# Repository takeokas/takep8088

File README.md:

# takep8088
8088 Single Board Computer  

## Spec  
- S-RAM 1MBytes  
--  全メモリ空間  
-- AS6C4008-55PCN (512KW×8bit)2チップ  
-- リセット直後は、メモリ空間の後半 512K は、ROM  
-- 出力ポートのアクセスで、後半512KをROM/RAM切り替え  

- ROM 64Bytes  
-- SST 27SF512(EEPROM)  
-- 27C512互換であれば使用可能、2764あたりからそのまま差し込めるはず  

- SIO 8251(USART)  
-- ジャンパ J1 で、ボーレート用クロックの周波数を選択可能  
-- 秋月で販売されている FTDI USBシリアル変換ケーブル(5V) が直接 差せる  
--  https://akizukidenshi.com/catalog/g/g105841/    

- フリーランニング・タイマ  
  18.75Hz / 9.375Hz を JP1 で、選択可能  

- Crystal 14.7456MHz  
-- 8251(USART) の baud rate generation に、いい感じの周波数  
-- CPU は、約 4.9MHz で動作  
-- 周辺IOのクロックは、約2.45MHz  

## ボード  

- ジャンパ J1  
-- 8251(USART)のボーレート・ジェネレータの周波数選択  
  19200/9600/4800 bps  (f/1の場合)  
  
- ジャンパ JP1  
-- フリーランニング・タイマの周期選択  
  18.75Hz / 9.375Hz

- ワイヤリング  

-- 8251 TX Empty割込みを使用する場合は、7405 の空き入力端子に、8251-TXE を接続する  
-- 7405 の空き入力ピンは、(手配線などで) 必ず GND へ、接続する。さもないと、Interrupt Enableした途端に、割込みが発生する。  
-- U20 74139が、74HC139 のときは、空き入力ピンを、DT-R、SS0 に接続すること。74LS139など TTL のときは、open のママでも支障ない。  

※ワイヤがあるのは、設計どおり  
-- PCBレイアウト中に、引き回しを諦めただけ…orz  

## 回路
### 7405: 割込み 要求  
-- 7405の入力は、反転されて、すべてワイアードORして反転して、8088のINT(割込み要求)に接続  
-- 7405のopenな端子は、自分で(手ハンダで?)、PullDownの必要あり  
-- 後から付けた機器からの割込み要求は、7405の空き端子に接続するとよい  

### 8251 TX Empty 割込み 要求  
-- 8251の RX割込みは、PCBで7405に接続済み  
-- 8251の TXE(empty)割込み使うよね!  
-- 自分で、7405 に配線してください ＼(^^;／  
-- PCBのレイアウトを諦めた=それが設計だっ  

### 余りゲート  
-- U1,74LS14: B(3,4),C(5,6),F(13,12)  
-- U12,74LS00: A(1,2,3),B(4,5,6)  
-- U24,74LS00: C(10,9,8),D(13,12,11)  
-- U23,74LS74: B(8-13)  

## IOポート  
###  IO port address  

   00-03 : usart0 (rw) USART レジスタ; 通常 00と01 を使用する  
   04-07 : sw1 (rd);  D0: SWの値を読む, D1: timerIRQ の確認  
   08-0B : timer-irq-clr (wr); timer IRQのクリア  
   0C-0F : sysreg (wr),D0:/rom0-ena=0でROM, 1でRAM1, D1:timer-int-ena=1でtimer割込み可, D2:led2, D3:led3  
  
   10-13 : inport2(rd),  D0: U18[2pin]=NC, D1:U18[4pin]=NC;U18=74LS367  
   14-17 :   
   18-1B :   
   1C-1F :   
   
### IO port 説明  
- sysreg (WR) 0x0C ; U5,74LS174  
-- D0: /rom0-ena (reset:0), 0:ROM0 / 1:RAM1 (メモリ空間後半 A19==1 を ROM/RAM切り替え)  
-- D1: timer-int-ena (reset:0), 0:disable / 1:enable  
-- D2: LED2 (resetで0, 点灯)  
-- D3: LED3 (resetで0, 点灯)  
-- D4: (U5 Q4)Open  
-- D5: (U5 Q5)Open  
  
- SW1 (RD) 0x04  
-- D0: SW  
-- D1 : free running timer IRQ 読み出し  
  
- timer-irq-clr  (WR) 0x08  
-- free running timer INT clear  
-- 1/(2^18) カウンタ割り込みクリア  
  
- inport2(rd) 0x10  
-- U18=74LS367  
-- D0: U18[2pin]=NC, D1:U18[4pin]=NC;  
-- D2: U18[6pin]=NC, D5:U18[10pin]=NC;   
※D3,D4 は飛ばしている(配線の困難性から)

## その他  
- HOLD を、Vcc に、手動で接続してみると、CPU の実行が停止し、HLDA LEDが点灯する  
- HOLD を使用する機器は、HOLD 端子に接続するとよい(PCB では、Pull Downしているのみ)
- 2026/MAR/20 「Kernel/VM探検隊＠つくば No3」での、発表資料  
--  https://www.slideshare.net/slideshow/tht-8088-single-board-computer-with-amd-8088-bought-at-junk-shop-in-1989/286593537?utm_source=clipboard_share_button&utm_campaign=slideshare_make_sharing_viral_v2&utm_variation=control&utm_medium=share
-

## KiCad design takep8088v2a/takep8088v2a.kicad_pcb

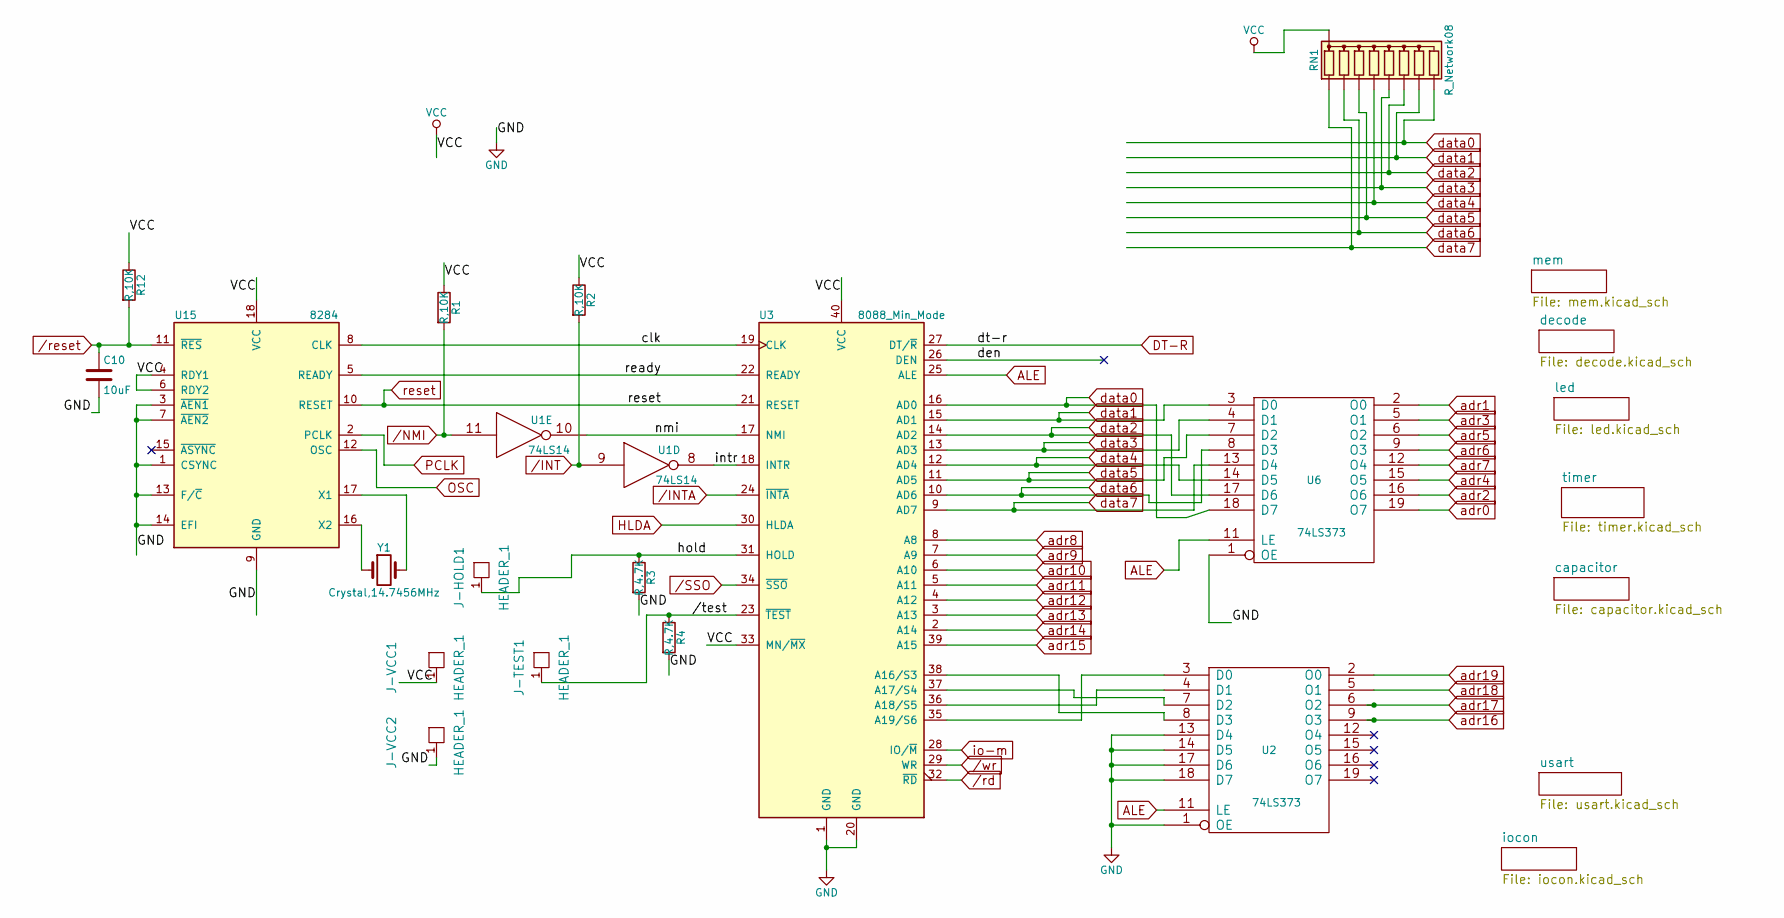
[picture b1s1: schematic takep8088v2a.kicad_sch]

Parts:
C10: 10uF; C_Disc_D3.0mm_W2.0mm_P2.50mm
J-HOLD1: HEADER_1; PinHeader_1x01_P2.54mm_Vertical
J-TEST1: HEADER_1; PinHeader_1x01_P2.54mm_Vertical
J-VCC1, J-VCC2: HEADER_1; PinHeader_1x01_P2.54mm_Vertical
R1, R2, R12: R,10K; R_Axial_DIN0207_L6.3mm_D2.5mm_P2.54mm_Vertical
R3, R4: R,4.7K; R_Axial_DIN0204_L3.6mm_D1.6mm_P5.08mm_Horizontal
RN1: R_Network08; R_Array_SIP9
U1: 74LS14; DIP-14_W7.62mm
U2, U6: 74LS373; DIP-20_W7.62mm
U3: 8088_Min_Mode; DIP-40_W15.24mm_Socket
U15: 8284; DIP-18_W7.62mm
Y1: Crystal,14.7456MHz; Crystal_HC49-4H_Vertical

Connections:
/clk: U3.19 (CLK), U15.8 (CLK)
/den: U3.26 (DEN)
/hold: J-HOLD1.1, R3.1, U3.31 (HOLD)
/intr: U1.8, U3.18 (INTR)
/nmi: U1.10, U3.17 (NMI)
/ready: U3.22 (READY), U15.5 (READY)
//test: J-TEST1.1, R4.1, U3.23 (~TEST)
ALE: U2.11 (LE), U3.25 (ALE), U6.11 (LE)
DT-R: U3.27 (DT/~R); also elsewhere on the board
GND: C10.2, J-VCC2.1, R3.2, R4.2, U1.7 (GND), U2.1 (OE), U2.10 (GND), U2.13 (D4), U2.14 (D5), U2.17 (D6), U2.18 (D7), U3.1 (GND), U3.20 (GND), U6.1 (OE), U6.10 (GND), U15.1 (CSYNC), U15.3 (~AEN1), U15.7 (~AEN2), U15.9 (GND), U15.13 (F/~C), U15.14 (EFI); also elsewhere on the board
HLDA: U3.30 (HLDA); also elsewhere on the board
unnamed: U2.3 (D0), U3.35 (A19/S6)
unnamed: U2.4 (D1), U3.36 (A18/S5)
unnamed: U2.7 (D2), U3.37 (A17/S4)
unnamed: U2.8 (D3), U3.38 (A16/S3)
unnamed: U15.17 (X1), Y1.2
unnamed: U15.16 (X2), Y1.1
OSC: U15.12 (OSC)
PCLK: U15.2 (PCLK); also elsewhere on the board
VCC: J-VCC1.1, R1.1, R2.1, R12.1, RN1.1 (common), U1.14 (VCC), U2.20 (VCC), U3.33 (MN/~MX), U3.40 (VCC), U6.20 (VCC), U15.4 (RDY1), U15.6 (RDY2), U15.18 (VCC); also elsewhere on the board
adr0: U6.19 (O7); also elsewhere on the board
adr1: U6.2 (O0); also elsewhere on the board
adr2: U6.16 (O6); also elsewhere on the board
adr3: U6.5 (O1); also elsewhere on the board
adr4: U6.15 (O5); also elsewhere on the board
adr5: U6.6 (O2); also elsewhere on the board
adr6: U6.9 (O3); also elsewhere on the board
adr7: U6.12 (O4); also elsewhere on the board
adr8: U3.8 (A8); also elsewhere on the board
adr9: U3.7 (A9); also elsewhere on the board
adr10: U3.6 (A10); also elsewhere on the board
adr11: U3.5 (A11); also elsewhere on the board
adr12: U3.4 (A12); also elsewhere on the board
adr13: U3.3 (A13); also elsewhere on the board
adr14: U3.2 (A14); also elsewhere on the board
adr15: U3.39 (A15); also elsewhere on the board
adr16: U2.9 (O3); also elsewhere on the board
adr17: U2.6 (O2); also elsewhere on the board
adr18: U2.5 (O1); also elsewhere on the board
adr19: U2.2 (O0); also elsewhere on the board
data0: RN1.9 (R8), U3.16 (AD0), U6.18 (D7); also elsewhere on the board
data1: RN1.8 (R7), U3.15 (AD1), U6.3 (D0); also elsewhere on the board
data2: RN1.7 (R6), U3.14 (AD2), U6.17 (D6); also elsewhere on the board
data3: RN1.6 (R5), U3.13 (AD3), U6.4 (D1); also elsewhere on the board
data4: RN1.5 (R4), U3.12 (AD4), U6.14 (D5); also elsewhere on the board
data5: RN1.4 (R3), U3.11 (AD5), U6.7 (D2); also elsewhere on the board
data6: RN1.3 (R2), U3.10 (AD6), U6.8 (D3); also elsewhere on the board
data7: RN1.2 (R1), U3.9 (AD7), U6.13 (D4); also elsewhere on the board
io-m: U3.28 (IO/~M); also elsewhere on the board
reset: U3.21 (RESET), U15.10 (RESET); also elsewhere on the board
/INT: R2.2, U1.9; also elsewhere on the board
/INTA: U3.24 (~INTA); also elsewhere on the board
/NMI: R1.2, U1.11; also elsewhere on the board
/SSO: U3.34 (~SSO); also elsewhere on the board
/rd: U3.32 (~RD); also elsewhere on the board
/reset: C10.1, R12.2, U15.11 (~RES); also elsewhere on the board
/wr: U3.29 (WR); also elsewhere on the board

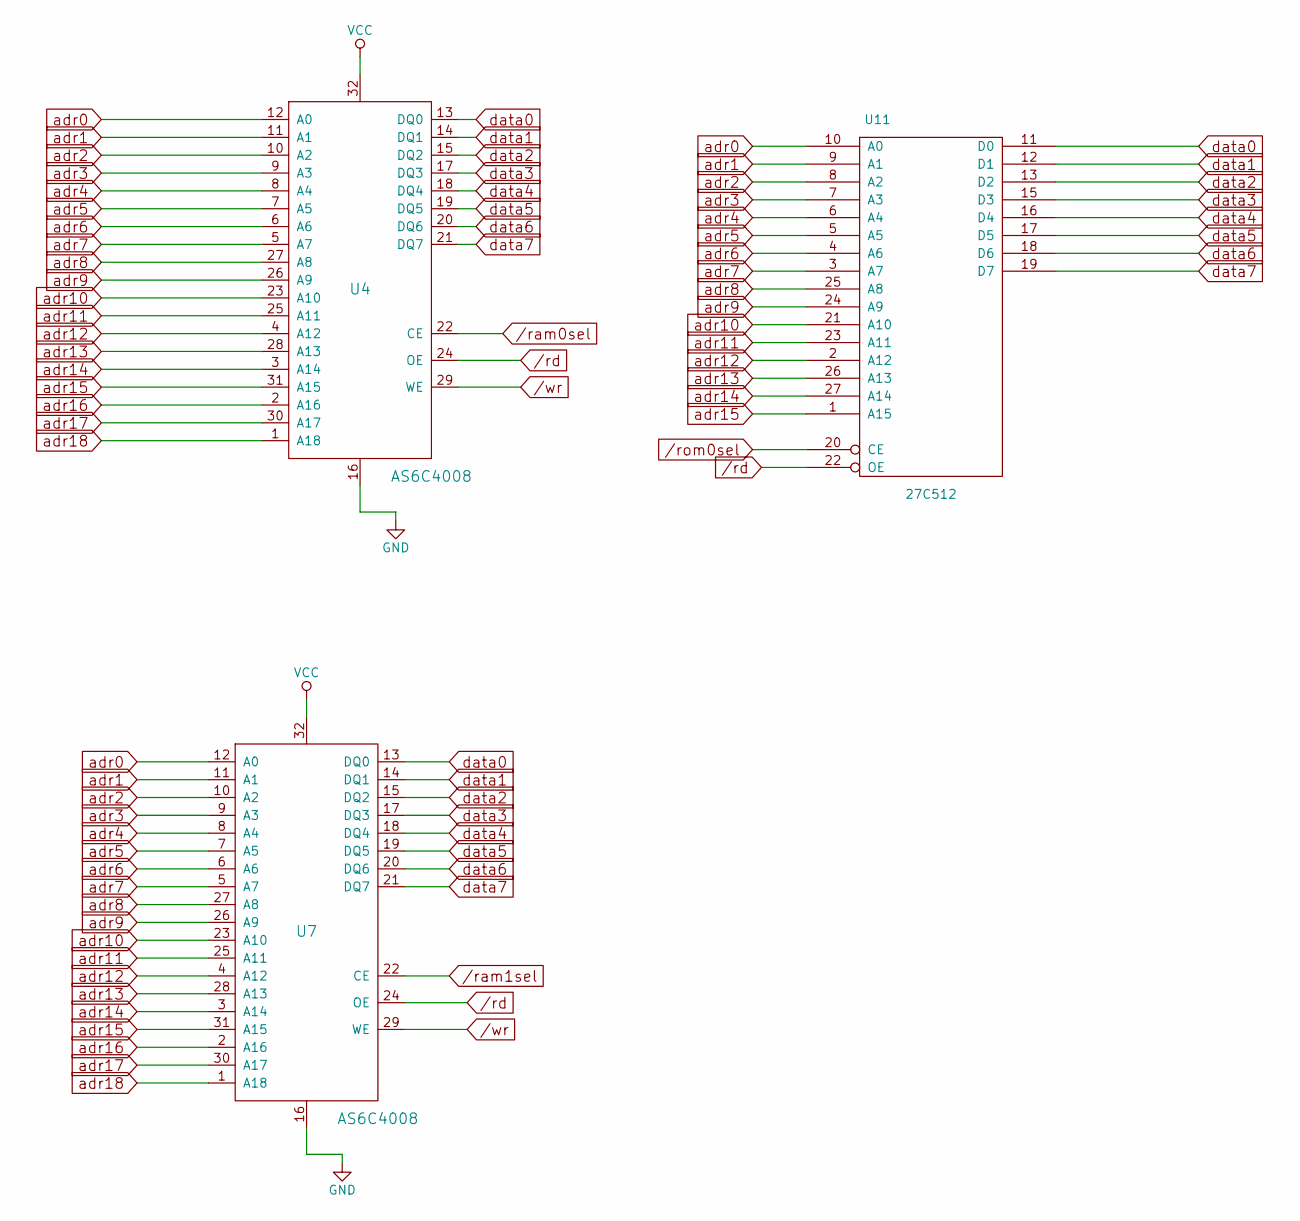
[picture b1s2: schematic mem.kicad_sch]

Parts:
U4, U7: AS6C4008; DIP-32_W15.24mm
U11: 27C512; DIP-28_W15.24mm

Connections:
GND: U4.16, U7.16, U11.14 (GND); also elsewhere on the board
VCC: U4.32, U7.32, U11.28 (VCC); also elsewhere on the board
adr0: U4.12 (A0), U7.12 (A0), U11.10 (A0); also elsewhere on the board
adr1: U4.11 (A1), U7.11 (A1), U11.9 (A1); also elsewhere on the board
adr2: U4.10 (A2), U7.10 (A2), U11.8 (A2); also elsewhere on the board
adr3: U4.9 (A3), U7.9 (A3), U11.7 (A3); also elsewhere on the board
adr4: U4.8 (A4), U7.8 (A4), U11.6 (A4); also elsewhere on the board
adr5: U4.7 (A5), U7.7 (A5), U11.5 (A5); also elsewhere on the board
adr6: U4.6 (A6), U7.6 (A6), U11.4 (A6); also elsewhere on the board
adr7: U4.5 (A7), U7.5 (A7), U11.3 (A7); also elsewhere on the board
adr8: U4.27 (A8), U7.27 (A8), U11.25 (A8); also elsewhere on the board
adr9: U4.26 (A9), U7.26 (A9), U11.24 (A9); also elsewhere on the board
adr10: U4.23 (A10), U7.23 (A10), U11.21 (A10); also elsewhere on the board
adr11: U4.25 (A11), U7.25 (A11), U11.23 (A11); also elsewhere on the board
adr12: U4.4 (A12), U7.4 (A12), U11.2 (A12); also elsewhere on the board
adr13: U4.28 (A13), U7.28 (A13), U11.26 (A13); also elsewhere on the board
adr14: U4.3 (A14), U7.3 (A14), U11.27 (A14); also elsewhere on the board
adr15: U4.31 (A15), U7.31 (A15), U11.1 (A15); also elsewhere on the board
adr16: U4.2 (A16), U7.2 (A16); also elsewhere on the board
adr17: U4.30 (A17), U7.30 (A17); also elsewhere on the board
adr18: U4.1 (A18), U7.1 (A18); also elsewhere on the board
data0: U4.13 (DQ0), U7.13 (DQ0), U11.11 (D0); also elsewhere on the board
data1: U4.14 (DQ1), U7.14 (DQ1), U11.12 (D1); also elsewhere on the board
data2: U4.15 (DQ2), U7.15 (DQ2), U11.13 (D2); also elsewhere on the board
data3: U4.17 (DQ3), U7.17 (DQ3), U11.15 (D3); also elsewhere on the board
data4: U4.18 (DQ4), U7.18 (DQ4), U11.16 (D4); also elsewhere on the board
data5: U4.19 (DQ5), U7.19 (DQ5), U11.17 (D5); also elsewhere on the board
data6: U4.20 (DQ6), U7.20 (DQ6), U11.18 (D6); also elsewhere on the board
data7: U4.21 (DQ7), U7.21 (DQ7), U11.19 (D7); also elsewhere on the board
/ram0sel: U4.22 (CE); also elsewhere on the board
/ram1sel: U7.22 (CE); also elsewhere on the board
/rd: U4.24 (OE), U7.24 (OE), U11.22 (OE); also elsewhere on the board
/rom0sel: U11.20 (CE); also elsewhere on the board
/wr: U4.29 (WE), U7.29 (WE); also elsewhere on the board

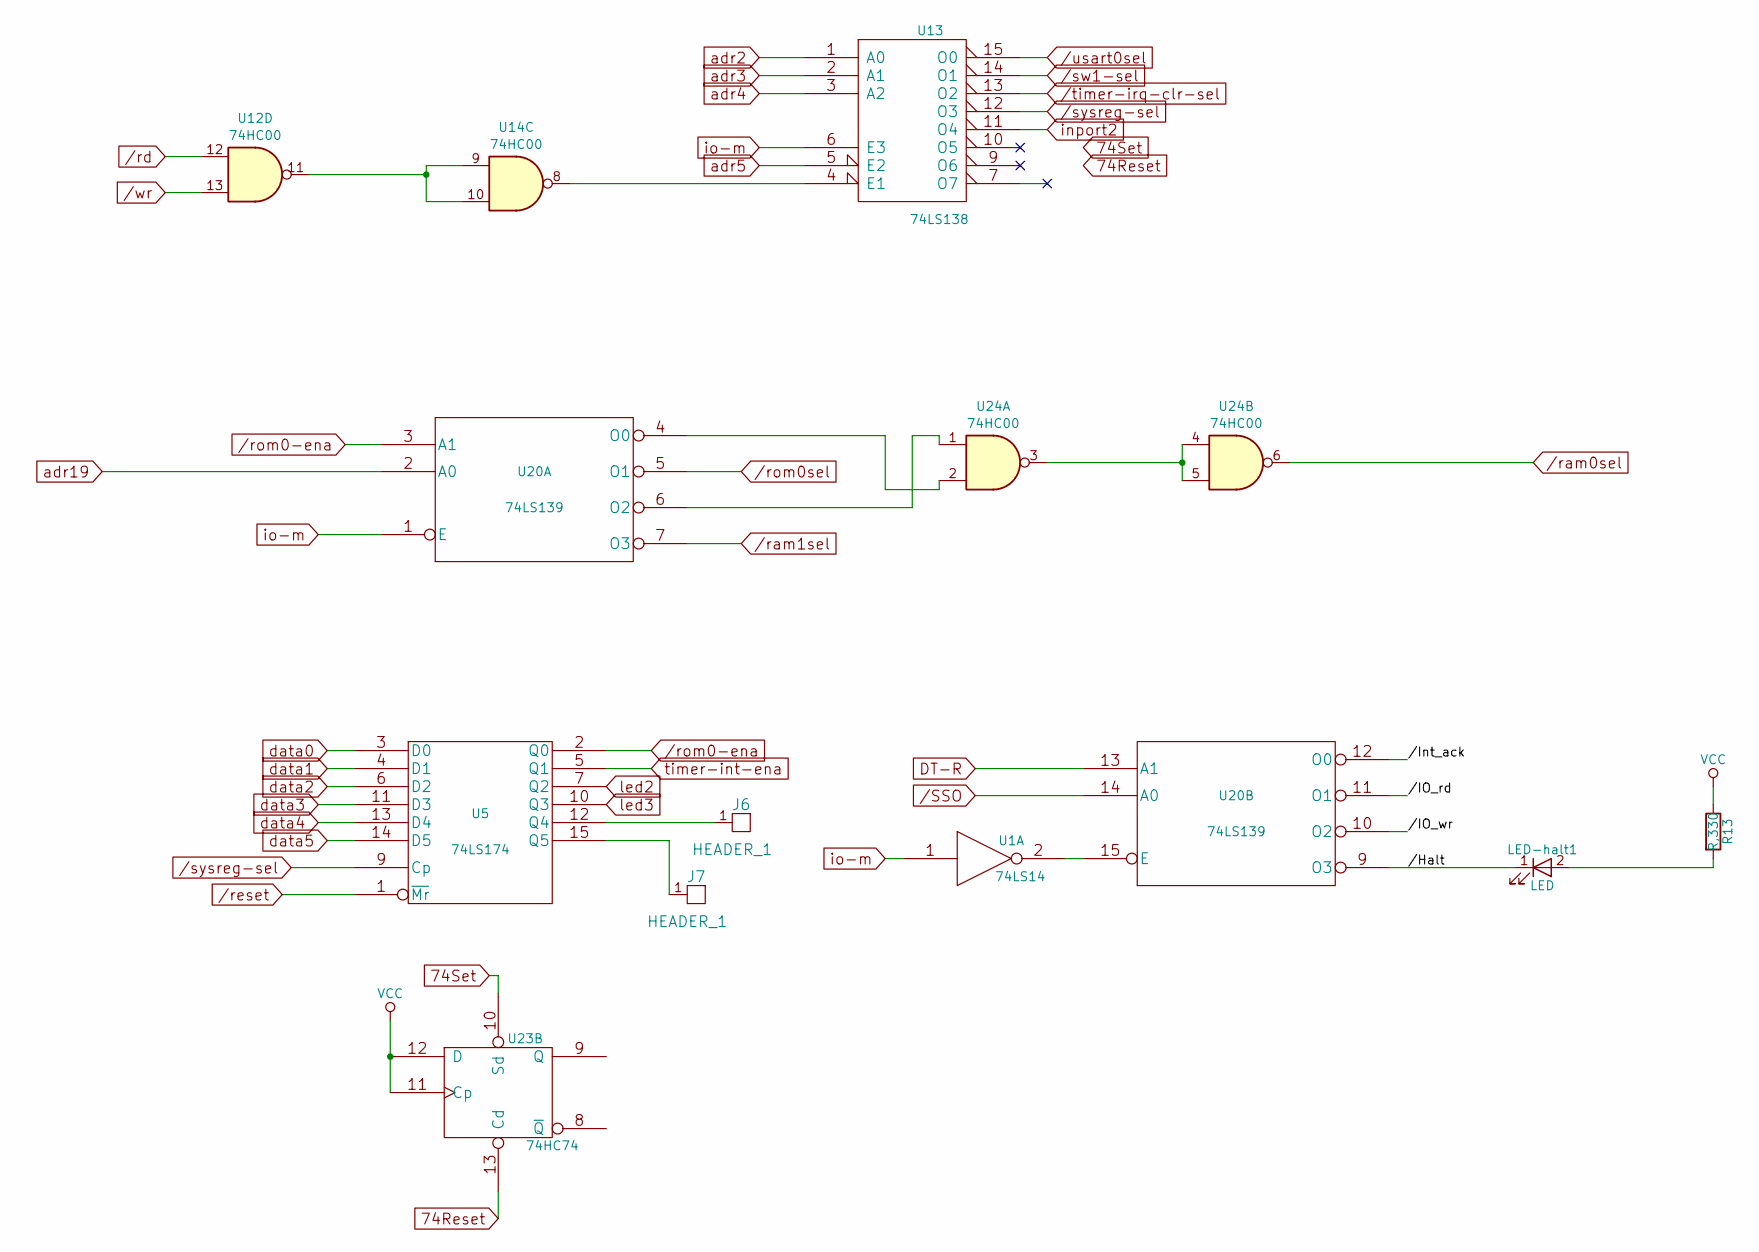
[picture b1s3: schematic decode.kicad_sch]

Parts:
J6, J7: HEADER_1; PinHeader_1x01_P2.54mm_Vertical
LED-halt1: LED; LED_D1.8mm_W3.3mm_H2.4mm
R13: R,330; R_Axial_DIN0207_L6.3mm_D2.5mm_P2.54mm_Vertical
U1: 74LS14; DIP-14_W7.62mm
U5: 74LS174; DIP-16_W7.62mm
U12, U14, U24: 74HC00
U13: 74LS138; DIP-16_W7.62mm
U20: 74LS139; DIP-16_W7.62mm
U23: 74HC74; DIP-14_W7.62mm

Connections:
74Reset: U23.13 (Cd)
74Set: U23.10 (Sd)
/decode//Halt: LED-halt1.1 (K), U20.9 (O3)
/decode//IO_rd: U20.11 (O1)
/decode//IO_wr: U20.10 (O2)
/decode//Int_ack: U20.12 (O0)
DT-R: U20.13 (A1); also elsewhere on the board
GND: U1.7 (GND), U5.8 (GND), U12.7 (GND), U13.8 (GND), U20.8 (GND), U23.7 (GND), U24.7 (GND); also elsewhere on the board
unnamed: LED-halt1.2 (A), R13.2
unnamed: J6.1, U5.12 (Q4)
unnamed: J7.1, U5.15 (Q5)
unnamed: U12.9, U12.10, U12.11, U14.9, U14.10
unnamed: U12.8, U13.4 (E1), U14.8
unnamed: U20.4 (O0), U24.2
unnamed: U20.6 (O2), U24.1
unnamed: U1.2, U20.15 (E)
unnamed: U24.3, U24.4, U24.5
VCC: R13.1, U1.14 (VCC), U5.16 (VCC), U12.14 (VCC), U13.16 (VCC), U20.16 (VCC), U23.11 (Cp), U23.12 (D), U23.14 (VCC), U24.14 (VCC); also elsewhere on the board
adr2: U13.1 (A0); also elsewhere on the board
adr3: U13.2 (A1); also elsewhere on the board
adr4: U13.3 (A2); also elsewhere on the board
adr5: U13.5 (E2); also elsewhere on the board
adr19: U20.2 (A0); also elsewhere on the board
data0: U5.3 (D0); also elsewhere on the board
data1: U5.4 (D1); also elsewhere on the board
data2: U5.6 (D2); also elsewhere on the board
data3: U5.11 (D3); also elsewhere on the board
data4: U5.13 (D4); also elsewhere on the board
data5: U5.14 (D5); also elsewhere on the board
inport2: U13.11 (O4); also elsewhere on the board
io-m: U1.1, U13.6 (E3), U20.1 (E); also elsewhere on the board
led2: U5.7 (Q2); also elsewhere on the board
led3: U5.10 (Q3); also elsewhere on the board
timer-int-ena: U5.5 (Q1); also elsewhere on the board
/SSO: U20.14 (A0); also elsewhere on the board
/ram0sel: U24.6; also elsewhere on the board
/ram1sel: U20.7 (O3); also elsewhere on the board
/rd: U12.12; also elsewhere on the board
/reset: U5.1 (~Mr); also elsewhere on the board
/rom0-ena: U5.2 (Q0), U20.3 (A1); also elsewhere on the board
/rom0sel: U20.5 (O1); also elsewhere on the board
/sw1-sel: U13.14 (O1); also elsewhere on the board
/sysreg-sel: U5.9 (Cp), U13.12 (O3)
/timer-irq-clr-sel: U13.13 (O2); also elsewhere on the board
/usart0sel: U13.15 (O0); also elsewhere on the board
/wr: U12.13; also elsewhere on the board

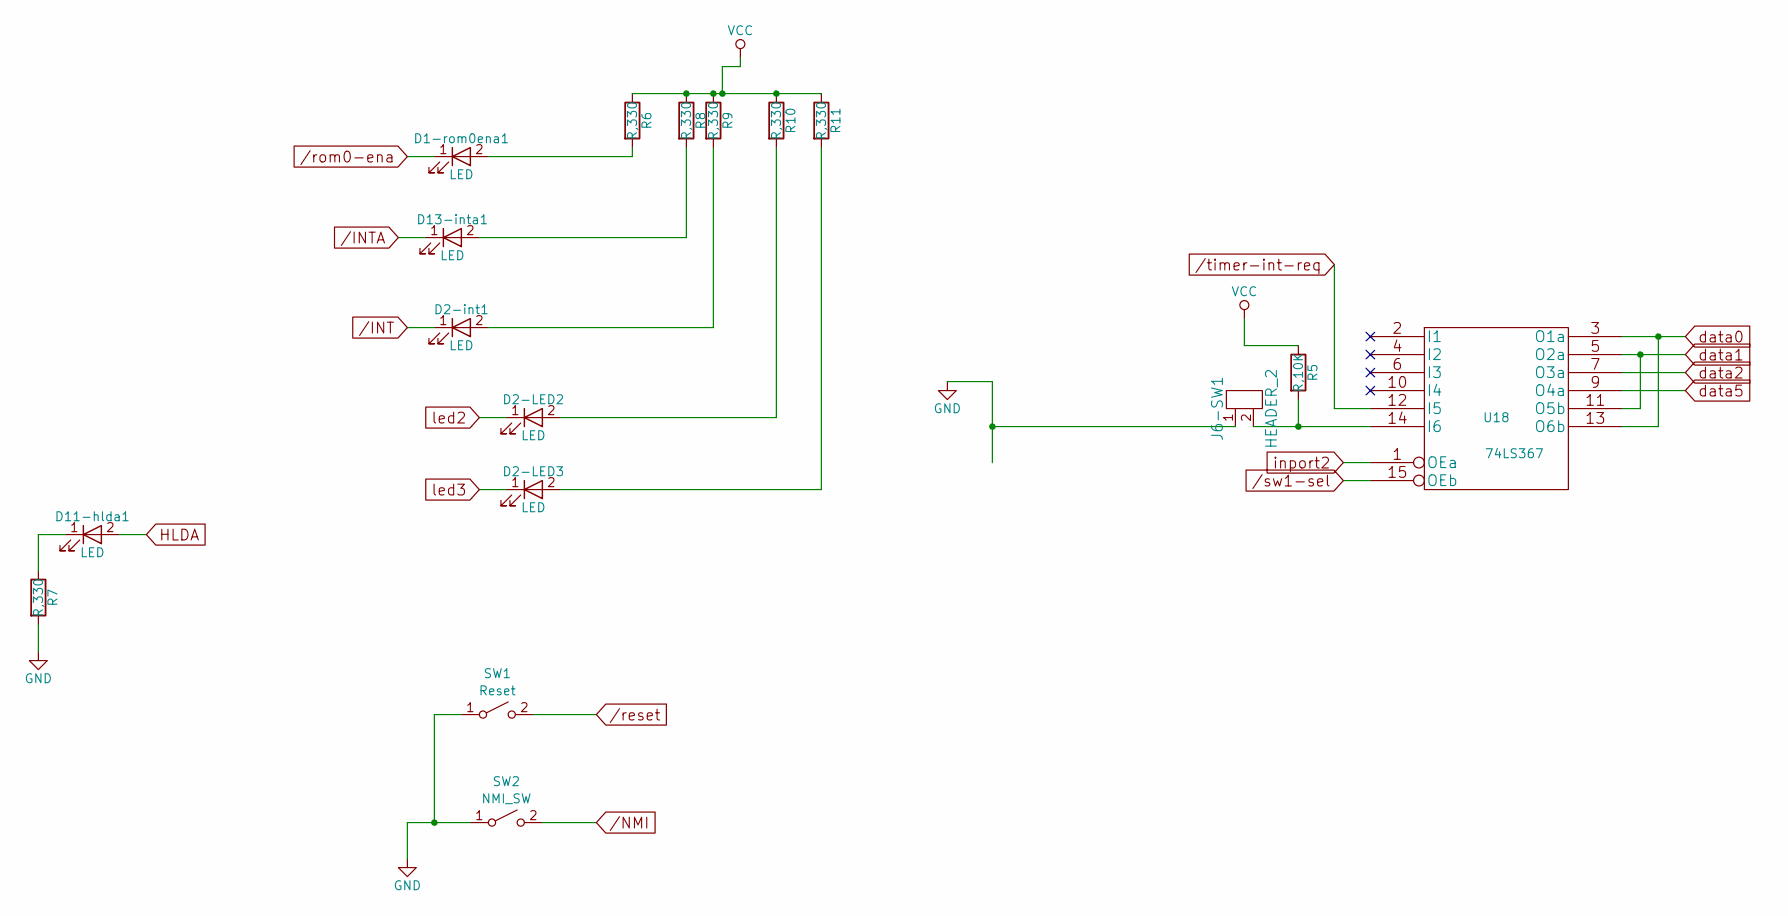
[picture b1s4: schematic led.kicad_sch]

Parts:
D1-rom0ena1, D2-LED2, D2-LED3, D2-int1, D11-hlda1, D13-inta1: LED; LED_D1.8mm_W3.3mm_H2.4mm
J6-SW1: HEADER_2; PinHeader_2x01_P2.54mm_Vertical
R5: R,10K; R_Axial_DIN0207_L6.3mm_D2.5mm_P2.54mm_Vertical
R6, R7, R8, R9, R10, R11: R,330; R_Axial_DIN0207_L6.3mm_D2.5mm_P2.54mm_Vertical
SW1: Reset; SW_PUSH_1P1T_6x3.5mm_H5.0_APEM_MJTP1250
SW2: NMI_SW; SW_PUSH_1P1T_6x3.5mm_H5.0_APEM_MJTP1250
U18: 74LS367; DIP-16_W7.62mm

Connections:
GND: J6-SW1.1, R7.2, SW1.1 (A), SW2.1 (A), U18.8 (GND); also elsewhere on the board
HLDA: D11-hlda1.2 (A); also elsewhere on the board
unnamed: D1-rom0ena1.2 (A), R6.2
unnamed: D2-LED2.2 (A), R10.2
unnamed: D2-LED3.2 (A), R11.2
unnamed: D2-int1.2 (A), R9.2
unnamed: D11-hlda1.1 (K), R7.1
unnamed: D13-inta1.2 (A), R8.2
unnamed: J6-SW1.2, R5.2, U18.14 (I6)
VCC: R5.1, R6.1, R8.1, R9.1, R10.1, R11.1, U18.16 (VCC); also elsewhere on the board
data0: U18.3 (O1a), U18.13 (O6b); also elsewhere on the board
data1: U18.5 (O2a), U18.11 (O5b); also elsewhere on the board
data2: U18.7 (O3a); also elsewhere on the board
data5: U18.9 (O4a); also elsewhere on the board
inport2: U18.1 (OEa); also elsewhere on the board
led2: D2-LED2.1 (K); also elsewhere on the board
led3: D2-LED3.1 (K); also elsewhere on the board
/INT: D2-int1.1 (K); also elsewhere on the board
/INTA: D13-inta1.1 (K); also elsewhere on the board
/NMI: SW2.2 (B); also elsewhere on the board
/reset: SW1.2 (B); also elsewhere on the board
/rom0-ena: D1-rom0ena1.1 (K); also elsewhere on the board
/sw1-sel: U18.15 (OEb); also elsewhere on the board
/timer-int-req: U18.12 (I5); also elsewhere on the board

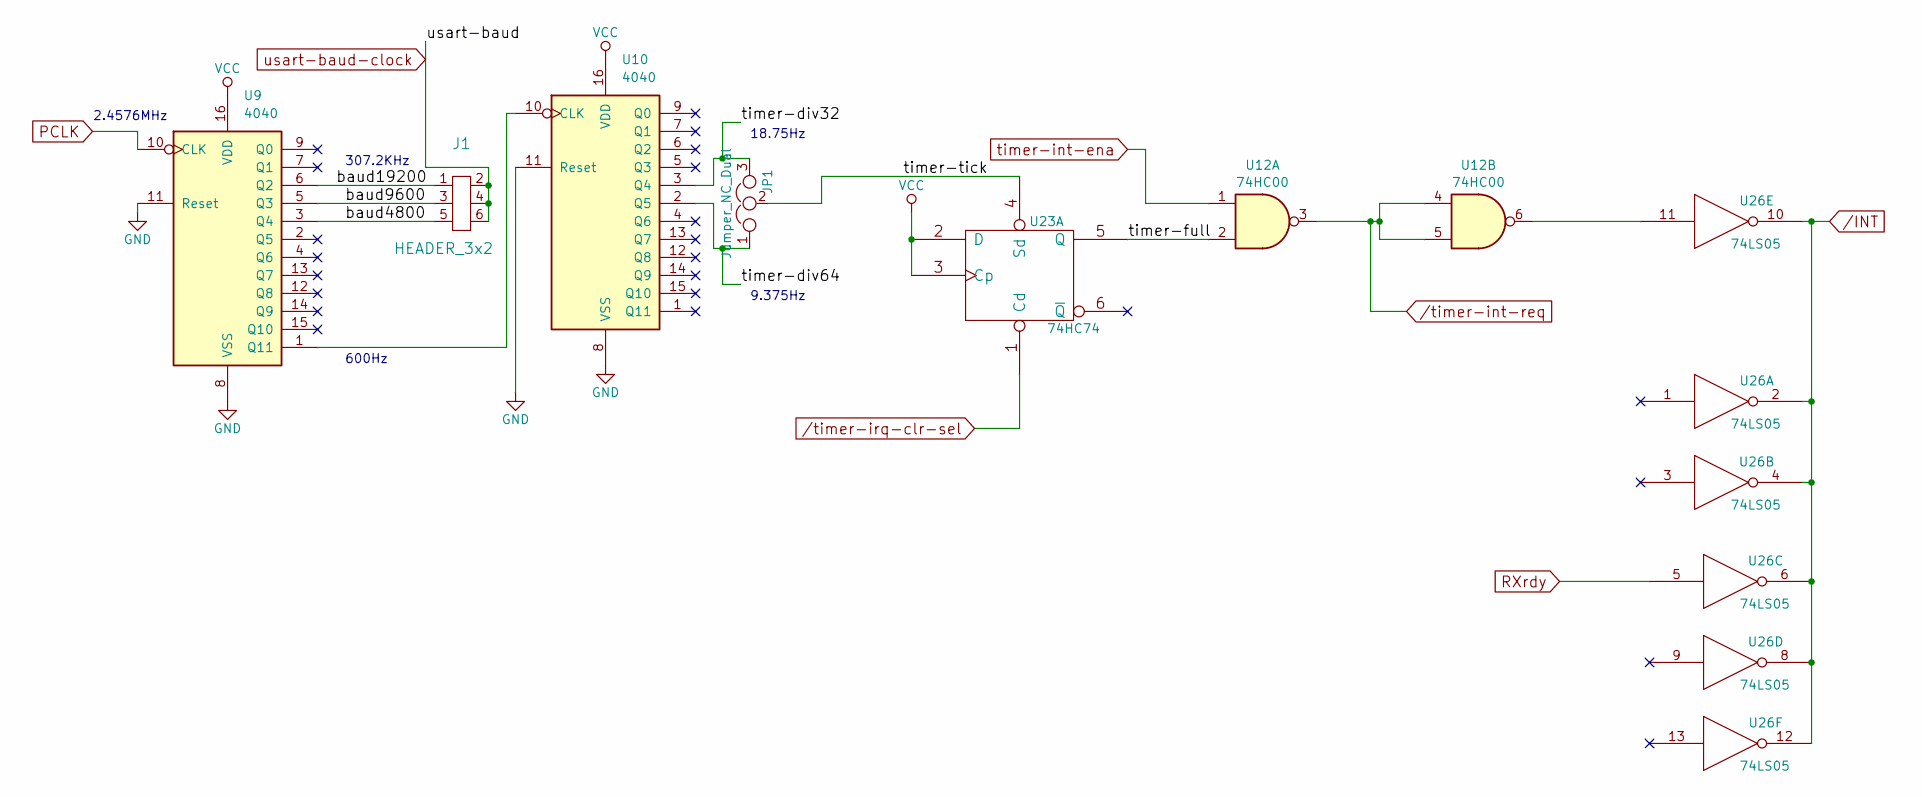
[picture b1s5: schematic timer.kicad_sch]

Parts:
J1: HEADER_3x2; PinHeader_2x03_P2.54mm_Vertical
JP1: Jumper_NC_Dual; PinHeader_1x03_P2.54mm_Vertical
U9, U10: 4040; DIP-16_W7.62mm
U12: 74HC00
U23: 74HC74; DIP-14_W7.62mm
U26: 74LS05; DIP-14_W7.62mm

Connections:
/timer/baud4800: J1.5, U9.3 (Q4)
/timer/baud9600: J1.3, U9.5 (Q3)
/timer/baud19200: J1.1, U9.6 (Q2)
/timer/timer-div32: JP1.3, U10.3 (Q4)
/timer/timer-div64: JP1.1, U10.2 (Q5)
/timer/timer-full: U12.2, U23.5 (Q)
/timer/timer-tick: JP1.2, U23.4 (Sd)
GND: U9.8 (VSS), U9.11 (Reset), U10.8 (VSS), U10.11 (Reset), U12.7 (GND), U23.7 (GND), U26.7 (GND); also elsewhere on the board
unnamed: U9.1 (Q11), U10.10 (CLK)
unnamed: U12.6, U26.11
unnamed 48: U12.9, U12.10; also elsewhere on the board
unnamed 49: U12.8; also elsewhere on the board
PCLK: U9.10 (CLK); also elsewhere on the board
RXrdy: U26.5; also elsewhere on the board
VCC: U9.16 (VDD), U10.16 (VDD), U12.14 (VCC), U23.2 (D), U23.3 (Cp), U23.14 (VCC), U26.14 (VCC); also elsewhere on the board
timer-int-ena: U12.1; also elsewhere on the board
usart-baud-clock: J1.2, J1.4, J1.6; also elsewhere on the board
/INT: U26.2, U26.4, U26.6, U26.8, U26.10, U26.12; also elsewhere on the board
/timer-int-req: U12.3, U12.4, U12.5; also elsewhere on the board
/timer-irq-clr-sel: U23.1 (Cd); also elsewhere on the board

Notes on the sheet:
600Hz
18.75Hz
2.4576MHz
9.375Hz
307.2KHz

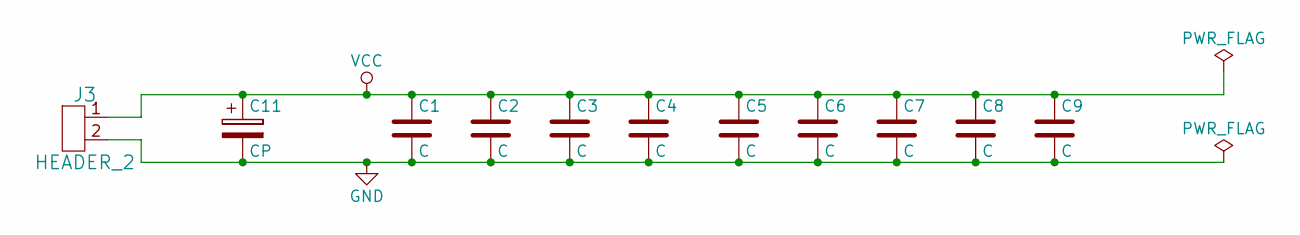
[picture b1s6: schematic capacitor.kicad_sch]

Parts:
C1, C2, C3, C4, C5, C6, C7, C8, C9: C; C_Disc_D3.0mm_W2.0mm_P2.50mm
C11: CP; C_Disc_D3.4mm_W2.1mm_P2.50mm
J3: HEADER_2; PinHeader_2x01_P2.54mm_Vertical

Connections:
GND: C1.2, C2.2, C3.2, C4.2, C5.2, C6.2, C7.2, C8.2, C9.2, C11.2, J3.2; also elsewhere on the board
VCC: C1.1, C2.1, C3.1, C4.1, C5.1, C6.1, C7.1, C8.1, C9.1, C11.1, J3.1; also elsewhere on the board

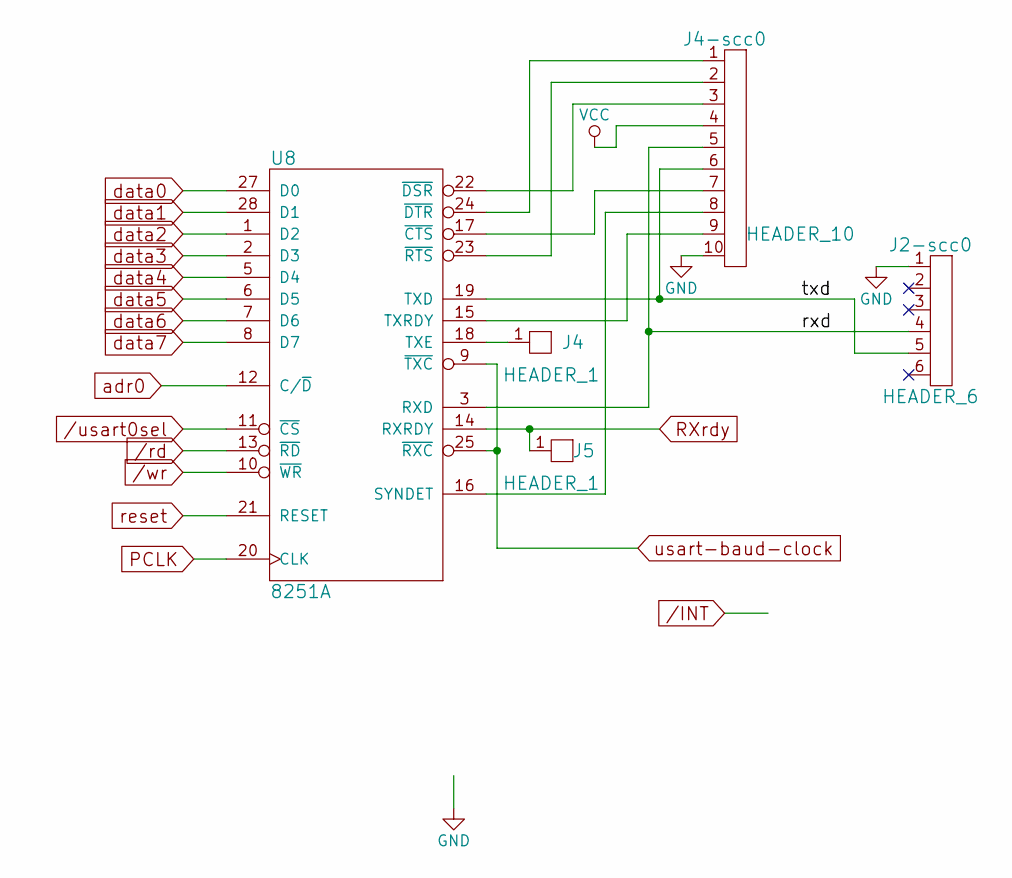
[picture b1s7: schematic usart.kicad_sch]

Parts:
J2-scc0: HEADER_6; PinHeader_1x06_P2.54mm_Vertical
J4, J5: HEADER_1; PinHeader_1x01_P2.54mm_Vertical
J4-scc0: HEADER_10; PinHeader_2x05_P2.54mm_Vertical
U8: 8251A; DIP-28_W15.24mm

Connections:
/usart/rxd: J2-scc0.4, J4-scc0.5, U8.3 (RXD)
/usart/txd: J2-scc0.5, J4-scc0.6, U8.19 (TXD)
GND: J2-scc0.1, J4-scc0.10, U8.4 (GND); also elsewhere on the board
unnamed: J4-scc0.8, U8.16 (SYNDET)
unnamed: J4.1, U8.18 (TXE)
unnamed: J4-scc0.9, U8.15 (TXRDY)
unnamed: J4-scc0.7, U8.17 (~CTS)
unnamed: J4-scc0.3, U8.22 (~DSR)
unnamed: J4-scc0.1, U8.24 (~DTR)
unnamed: J4-scc0.2, U8.23 (~RTS)
PCLK: U8.20 (CLK); also elsewhere on the board
RXrdy: J5.1, U8.14 (RXRDY); also elsewhere on the board
VCC: J4-scc0.4, U8.26 (VCC); also elsewhere on the board
adr0: U8.12 (C/~D); also elsewhere on the board
data0: U8.27 (D0); also elsewhere on the board
data1: U8.28 (D1); also elsewhere on the board
data2: U8.1 (D2); also elsewhere on the board
data3: U8.2 (D3); also elsewhere on the board
data4: U8.5 (D4); also elsewhere on the board
data5: U8.6 (D5); also elsewhere on the board
data6: U8.7 (D6); also elsewhere on the board
data7: U8.8 (D7); also elsewhere on the board
reset: U8.21 (RESET); also elsewhere on the board
usart-baud-clock: U8.9 (~TXC), U8.25 (~RXC); also elsewhere on the board
/rd: U8.13 (~RD); also elsewhere on the board
/usart0sel: U8.11 (~CS); also elsewhere on the board
/wr: U8.10 (~WR); also elsewhere on the board

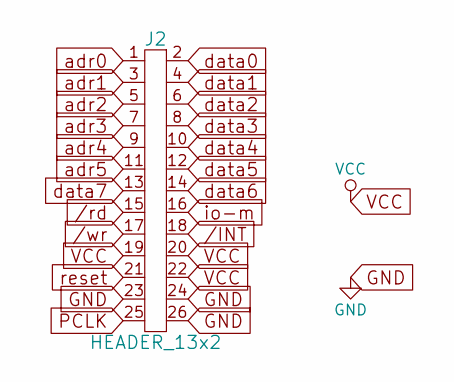
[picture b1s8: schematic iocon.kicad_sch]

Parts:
J2: HEADER_13x2; PinHeader_2x13_P2.54mm_Vertical

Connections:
GND: J2.23, J2.24, J2.26; also elsewhere on the board
PCLK: J2.25; also elsewhere on the board
VCC: J2.19, J2.20, J2.22; also elsewhere on the board
adr0: J2.1; also elsewhere on the board
adr1: J2.3; also elsewhere on the board
adr2: J2.5; also elsewhere on the board
adr3: J2.7; also elsewhere on the board
adr4: J2.9; also elsewhere on the board
adr5: J2.11; also elsewhere on the board
data0: J2.2; also elsewhere on the board
data1: J2.4; also elsewhere on the board
data2: J2.6; also elsewhere on the board
data3: J2.8; also elsewhere on the board
data4: J2.10; also elsewhere on the board
data5: J2.12; also elsewhere on the board
data6: J2.14; also elsewhere on the board
data7: J2.13; also elsewhere on the board
io-m: J2.16; also elsewhere on the board
reset: J2.21; also elsewhere on the board
/INT: J2.18; also elsewhere on the board
/rd: J2.15; also elsewhere on the board
/wr: J2.17; also elsewhere on the board

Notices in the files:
takep8088v2a/takep8088v2a.kicad_pcb:
©2025,2026
